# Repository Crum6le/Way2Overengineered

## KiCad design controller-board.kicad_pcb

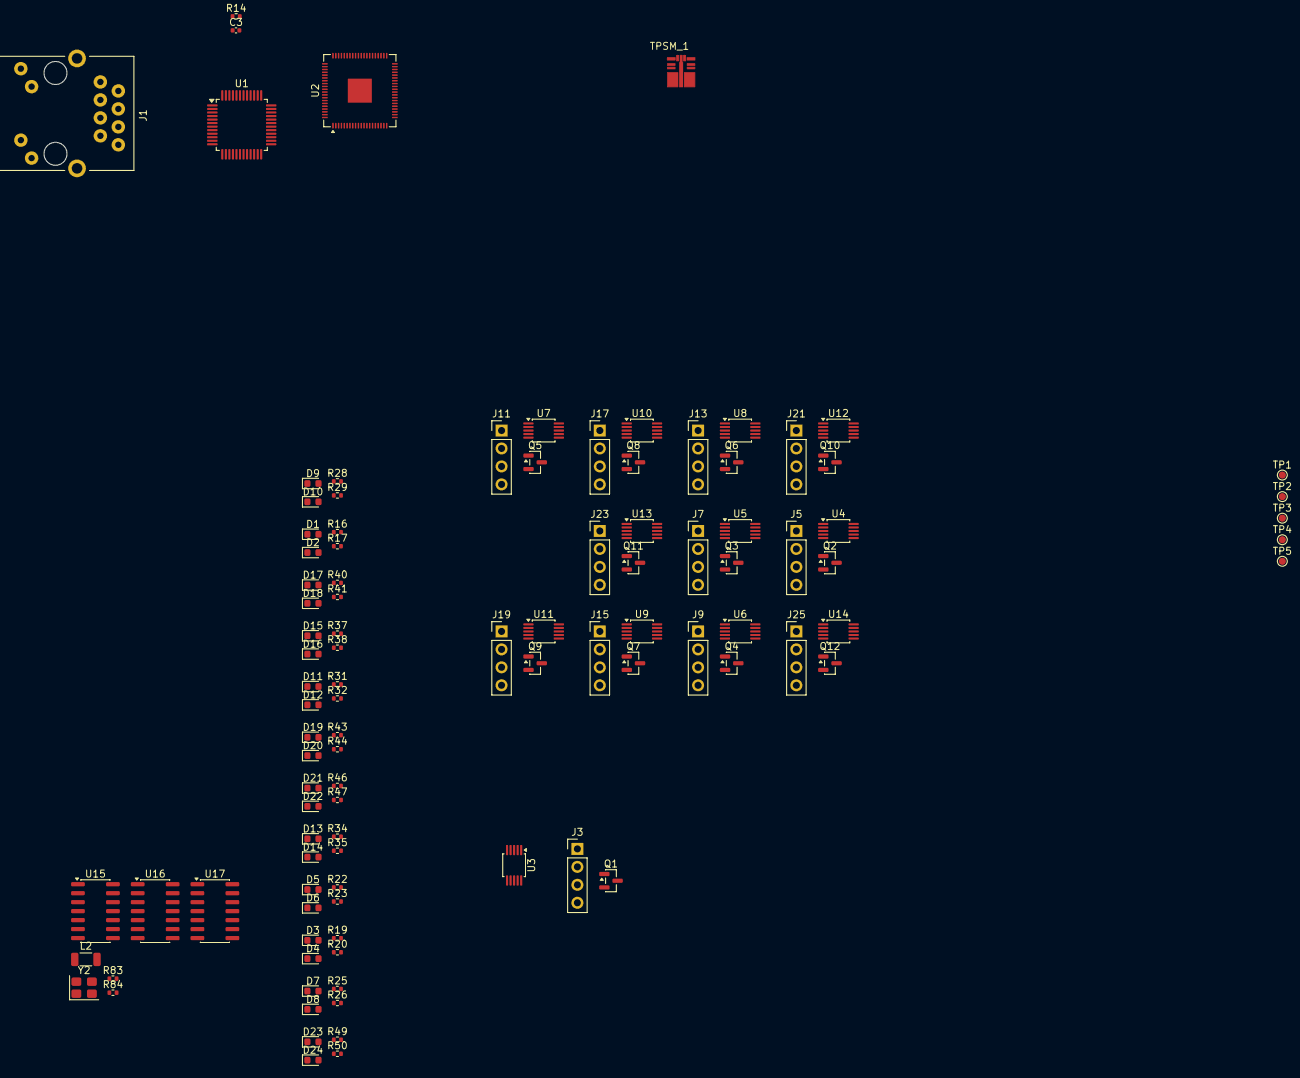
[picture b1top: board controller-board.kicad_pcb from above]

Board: 4 copper layers, 102 parts (0 on the bottom side), 105 nets, no tracks yet.

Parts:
C3: 100n; C_0402_1005Metric
D1, D2, D3, D4, D5, D6, D7, D8, D9, D10, D11, D12, D13, D14, D15, D16, D17, D18, D19, D20, D21, D22, D23, D24: LED; LED_0603_1608Metric
J1: RJ45_RB1-125BAG1A; RJ45_UDE_RB1-125BAG1A
J3, J5, J7, J9, J11, J13, J15, J17, J19, J21, J23, J25: Molex; PinHeader_1x04_P2.54mm_Vertical
L2: APBD3216-121WTD12; L_1206_3216Metric
Q1, Q2, Q3, Q4, Q5, Q6, Q7, Q8, Q9, Q10, Q11, Q12: BSS138; SOT-23
R14: 1M; R_0402_1005Metric
R16, R17, R19, R20, R22, R23, R25, R26, R28, R29, R31, R32, R34, R35, R37, R38, R40, R41, R43, R44, R46, R47, R49, R50, R83, R84: 100R; R_0402_1005Metric
TP1: SCLK; TestPoint_Pad_D1.0mm
TP2: SWDIO; TestPoint_Pad_D1.0mm
TP3: Reset; TestPoint_Pad_D1.0mm
TP4, TP5: GND; TestPoint_Pad_D1.0mm
TPSM_1: TPSM_3360
U1: W5500; LQFP-48_7x7mm_P0.5mm
U2: RP2350B; QFN-80-1EP_10x10mm_P0.4mm_EP3.4x3.4mm
U3, U4, U5, U6, U7, U8, U9, U10, U11, U12, U13, U14: INA226; TSSOP-10_3x3mm_P0.5mm
U15, U16, U17: 74HC164; SO-14_3.9x8.65mm_P1.27mm
Y2: abm8-272-t3; Crystal_SMD_3225-4Pin_3.2x2.5mm

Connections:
1V1D: U2.10 (DVDD), U2.32 (DVDD), U2.51 (DVDD), U2.65 (VREG_FB)
3V3A: L2.1, U1.4 (AVDD), U1.8 (AVDD), U1.11 (AVDD), U1.15 (AVDD), U1.17 (AVDD), U1.21 (AVDD)
3V3D: J1.L1, J1.L3, L2.2, Q1.1 (G), Q2.1 (G), Q3.1 (G), Q4.1 (G), Q5.1 (G), Q6.1 (G), Q7.1 (G), Q8.1 (G), Q9.1 (G), Q10.1 (G), Q11.1 (G), Q12.1 (G), U1.28 (VDD), U2.5 (IOVDD), U2.15 (IOVDD), U2.24 (IOVDD), U2.29 (IOVDD), U2.41 (IOVDD), U2.50 (IOVDD), U2.60 (IOVDD), U2.64 (VREG_VIN), U2.68 (USB_OTP_VDD), U2.69 (QSPI_IOVDD), U2.76 (IOVDD), U3.6 (VS), U4.1 (A1), U4.6 (VS), U5.6 (VS), U6.2 (A0), U6.6 (VS), U7.1 (A1), U7.2 (A0), U7.6 (VS), U8.2 (A0), U8.6 (VS), U9.6 (VS), U10.1 (A1), U10.6 (VS), U11.6 (VS), U12.6 (VS), U13.1 (A1), U13.6 (VS), U14.6 (VS), U15.1 (DSA), U15.14 (VCC), U16.1 (DSA), U16.14 (VCC), U17.1 (DSA), U17.14 (VCC)
/LEDPin1/LED1: D3.2 (A), U17.3 (Q0)
/LEDPin1/LED2: D4.2 (A), U17.4 (Q1)
/LEDPin2/LED1: D5.2 (A), U15.3 (Q0)
/LEDPin2/LED2: D6.2 (A), U15.4 (Q1)
/LEDPin3/LED1: D7.2 (A), U16.5 (Q2)
/LEDPin3/LED2: D8.2 (A), U16.6 (Q3)
/LEDPin4/LED1: D9.2 (A), U17.5 (Q2)
/LEDPin4/LED2: D10.2 (A), U17.6 (Q3)
/LEDPin5/LED1: D11.2 (A), U15.5 (Q2)
/LEDPin5/LED2: D12.2 (A), U15.6 (Q3)
/LEDPin6/LED1: D13.2 (A), U16.10 (Q4)
/LEDPin6/LED2: D14.2 (A), U16.11 (Q5)
/LEDPin7/LED1: D15.2 (A), U17.10 (Q4)
/LEDPin7/LED2: D16.2 (A), U17.11 (Q5)
/LEDPin8/LED1: D17.2 (A), U15.10 (Q4)
/LEDPin8/LED2: D18.2 (A), U15.11 (Q5)
/LEDPin9/LED1: D19.2 (A), U16.12 (Q6)
/LEDPin9/LED2: D20.2 (A), U16.13 (Q7)
/LEDPin10/LED1: D21.2 (A), U17.12 (Q6)
/LEDPin10/LED2: D22.2 (A), U17.13 (Q7)
/LEDPin11/LED1: D23.2 (A), U15.12 (Q6)
/LEDPin11/LED2: D24.2 (A), U15.13 (Q7)
/LEDPin/LED1: D1.2 (A), U16.3 (Q0)
/LEDPin/LED2: D2.2 (A), U16.4 (Q1)
CP_CH1: U2.22 (GPIO22), U16.8 (CP)
CP_CH2: U2.26 (GPIO25), U17.8 (CP)
CP_CH3: U2.36 (GPIO28), U15.8 (CP)
DATA_1: Q1.2 (S), U2.6 (GPIO8)
DATA_2: Q4.2 (S), U2.7 (GPIO9)
DATA_3: Q7.2 (S), U2.8 (GPIO10)
DATA_4: Q10.2 (S), U2.9 (GPIO11)
DATA_5: Q2.2 (S), U2.11 (GPIO12)
DATA_6: Q5.2 (S), U2.12 (GPIO13)
DATA_7: Q8.2 (S), U2.13 (GPIO14)
DATA_8: Q11.2 (S), U2.14 (GPIO15)
DATA_9: Q3.2 (S), U2.16 (GPIO16)
DATA_10: Q6.2 (S), U2.17 (GPIO17)
DATA_11: Q9.2 (S), U2.18 (GPIO18)
DATA_12: Q12.2 (S), U2.19 (GPIO19)
GND: C3.2, J3.1, J5.1, J7.1, J9.1, J11.1, J13.1, J15.1, J17.1, J19.1, J21.1, J23.1, J25.1, R16.2, R17.2, R19.2, R20.2, R22.2, R23.2, R25.2, R26.2, R28.2, R29.2, R31.2, R32.2, R34.2, R35.2, R37.2, R38.2, R40.2, R41.2, R43.2, R44.2, R46.2, R47.2, R49.2, R50.2, TP4.1 (1_1), TP5.1 (1_1), TPSM_1.10 (GND), TPSM_1.11 (MODE/SYNC), U1.3 (AGND), U1.9 (AGND), U1.14 (AGND), U1.16 (AGND), U1.19 (AGND), U1.29 (GND), U1.48 (AGND), U2.62 (VREG_PGND), U2.81 (GND), U3.1 (A1), U3.2 (A0), U3.7 (GND), U4.2 (A0), U4.7 (GND), U5.2 (A0), U5.7 (GND), U6.1 (A1), U6.7 (GND), U7.7 (GND), U8.7 (GND), U9.1 (A1), U9.7 (GND), U10.7 (GND), U11.7 (GND), U12.1 (A1), U12.7 (GND), U13.7 (GND), U14.7 (GND), U15.7 (GND), U16.7 (GND), U17.7 (GND), Y2.2 (G), Y2.4 (G)
INTn: U1.36 (~INT), U2.1 (GPIO4)
IN_CH1: U2.21 (GPIO21), U16.2 (DSB)
IN_CH2: U2.25 (GPIO24), U17.2 (DSB)
IN_CH3: U2.28 (GPIO27), U15.2 (DSB)
MISO: U1.35 (MOSI), U2.77 (GPIO0)
MOSI: U1.34 (MISO), U2.80 (GPIO3)
MRn_CH1: U2.20 (GPIO20), U16.9 (~MR)
MRn_CH2: U2.23 (GPIO23), U17.9 (~MR)
MRn_CH3: U2.27 (GPIO26), U15.9 (~MR)
unnamed: D1.1 (K), R16.1
unnamed: D2.1 (K), R17.1
unnamed: D3.1 (K), R19.1
unnamed: D4.1 (K), R20.1
unnamed: D5.1 (K), R22.1
unnamed: D6.1 (K), R23.1
unnamed: D7.1 (K), R25.1
unnamed: D8.1 (K), R26.1
unnamed: D9.1 (K), R28.1
unnamed: D10.1 (K), R29.1
unnamed: D11.1 (K), R31.1
unnamed: D12.1 (K), R32.1
unnamed: D13.1 (K), R34.1
unnamed: D14.1 (K), R35.1
unnamed: D15.1 (K), R37.1
unnamed: D16.1 (K), R38.1
unnamed: D17.1 (K), R40.1
unnamed: D18.1 (K), R41.1
unnamed: D19.1 (K), R43.1
unnamed: D20.1 (K), R44.1
unnamed: D21.1 (K), R46.1
unnamed: D22.1 (K), R47.1
unnamed: D23.1 (K), R49.1
unnamed: D24.1 (K), R50.1
unnamed: C3.1, J1.R3 (CT)
unnamed: J3.2, Q1.3 (D)
unnamed: J5.2, Q2.3 (D)
unnamed: J7.2, Q3.3 (D)
unnamed: J9.2, Q4.3 (D)
unnamed: J11.2, Q5.3 (D)
unnamed: J13.2, Q6.3 (D)
unnamed: J15.2, Q7.3 (D)
unnamed: J17.2, Q8.3 (D)
unnamed: J19.2, Q9.3 (D)
unnamed: J21.2, Q10.3 (D)
unnamed: J23.2, Q11.3 (D)
unnamed: J25.2, Q12.3 (D)
unnamed: R83.1, TP1.1 (1_1)
unnamed: R84.1, TP2.1 (1_1)
unnamed: R14.2, U1.30 (XI/CLKIN)
unnamed: R14.1, U1.31 (XO)
unnamed: TP3.1 (1_1), U2.35 (RUN)
unnamed: R83.2, U2.33 (SWCLK)
unnamed: R84.2, U2.34 (SWDIO)
unnamed: U2.30 (XIN), Y2.1
RSTn_ETH: U1.37 (~RST), U2.2 (GPIO5)
SCL: U2.4 (GPIO7), U3.5 (SCL), U4.5 (SCL), U5.5 (SCL), U6.5 (SCL), U7.5 (SCL), U8.5 (SCL), U9.5 (SCL), U10.5 (SCL), U11.5 (SCL), U12.2 (A0), U12.5 (SCL), U13.2 (A0), U13.5 (SCL), U14.2 (A0), U14.5 (SCL)
SCLK: U1.33 (SCLK), U2.79 (GPIO2)
SCSn: U1.32 (~SCS), U2.78 (GPIO1)
SDA: U2.3 (GPIO6), U3.4 (SDA), U4.4 (SDA), U5.1 (A1), U5.4 (SDA), U6.4 (SDA), U7.4 (SDA), U8.1 (A1), U8.4 (SDA), U9.2 (A0), U9.4 (SDA), U10.2 (A0), U10.4 (SDA), U11.1 (A1), U11.2 (A0), U11.4 (SDA), U12.4 (SDA), U13.4 (SDA), U14.1 (A1), U14.4 (SDA)
VCC: TPSM_1.2 (EN), TPSM_1.3 (VIN)
VIN: U3.8 (Vbus), U4.8 (Vbus), U5.8 (Vbus), U6.8 (Vbus), U7.8 (Vbus), U8.8 (Vbus), U9.8 (Vbus), U10.8 (Vbus), U11.8 (Vbus), U12.8 (Vbus), U13.8 (Vbus), U14.8 (Vbus)
VOUT: TPSM_1.4 (VOUT), TPSM_1.9 (FB)
